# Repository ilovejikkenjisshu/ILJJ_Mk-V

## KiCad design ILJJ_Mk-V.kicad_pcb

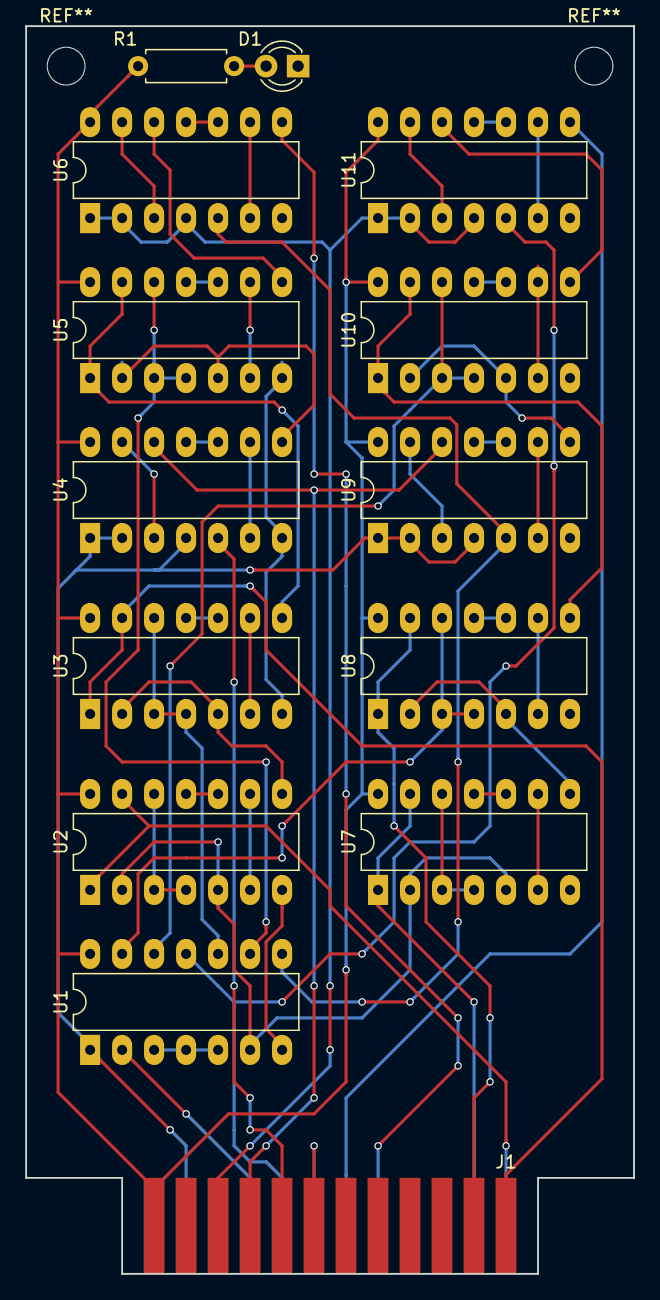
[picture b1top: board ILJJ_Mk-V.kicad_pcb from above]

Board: 2 copper layers, 48.3 x 99.1 mm, 14 parts (0 on the bottom side), 55 nets.

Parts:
D1: POWER; LED_D3.0mm
J1: Conn_02x12; 5530843-1_edge
R1: R; R_Axial_DIN0207_L6.3mm_D2.5mm_P7.62mm_Horizontal
U1, U2, U3, U4, U5, U6, U7, U8, U9, U10, U11: 74LS00; DIP-14_W7.62mm_LongPads

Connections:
/A0: J1.23, U3.1, U3.13
/A1: J1.21, U8.1, U8.13
/B0: J1.24, U2.1, U2.13
/B1: J1.22, U7.1, U7.13
/Cin: J1.9, U4.5
/Cout: J1.10, U1.11, U11.5
/F0: J1.7, J1.8, U1.2, U4.12, U9.12
/F1: J1.5, J1.6, U6.1, U6.2, U6.4, U11.1, U11.2, U11.4
/F2: J1.3, J1.4, U1.1, U4.1, U4.2, U4.4, U9.1, U9.2, U9.4
/FA0_B: U2.8, U3.2, U3.5
/FA0_Cin: U4.8, U5.2, U5.5
/FA0_S: U5.8, U6.12
/FA1_B: U7.8, U8.2, U8.5
/FA1_Cin: U9.8, U10.2, U10.5
/FA1_S: U10.8, U11.12
/IBC: U1.8, U6.5, U9.5
/S0: J1.16, U6.8
/S1: J1.14, U11.8
/SUB_FLAG: U1.6, U2.2, U2.5, U7.2, U7.5
GND: D1.1, J1.11, J1.12, U1.7, U2.7, U3.7, U4.7, U5.7, U6.7, U7.7, U8.7, U9.7, U10.7, U11.7
unnamed: D1.2, R1.2
unnamed: U1.3, U1.4, U1.5
unnamed: U1.9, U5.3, U5.4, U5.12
unnamed: U1.10, U3.3, U3.4, U3.12
unnamed: U1.12, U10.3, U10.4, U10.12
unnamed: U1.13, U8.3, U8.4, U8.12
unnamed: U2.6, U2.9
unnamed: U2.10, U2.11
unnamed: U2.3, U2.4, U2.12
unnamed: U3.6, U3.9
unnamed: U3.8, U5.1, U5.13
unnamed: U3.10, U3.11
unnamed: U4.6, U4.9
unnamed: U4.10, U4.11
unnamed: U4.3, U4.13
unnamed: U5.6, U5.9
unnamed: U5.10, U5.11
unnamed: U6.6, U6.9
unnamed: U6.10, U6.11
unnamed: U6.3, U6.13
unnamed: U7.6, U7.9
unnamed: U7.10, U7.11
unnamed: U7.3, U7.4, U7.12
unnamed: U8.6, U8.9
unnamed: U8.10, U8.11
unnamed: U9.6, U9.9
unnamed: U9.10, U9.11
unnamed: U9.3, U9.13
unnamed: U8.8, U10.1, U10.13
unnamed: U10.6, U10.9
unnamed: U10.10, U10.11
unnamed: U11.6, U11.9
unnamed: U11.10, U11.11
unnamed: U11.3, U11.13
VCC: J1.1, J1.2, R1.1, U1.14, U2.14, U3.14, U4.14, U5.14, U6.14, U7.14, U8.14, U9.14, U10.14, U11.14

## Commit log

2018-10-15 [add] 基本的な回路図
    アノテーションはまだ
2018-10-15 [add] アノテーションとIC電源
    ERCも通した
2018-10-15 [add] カードエッジ部のフットプリント
2018-10-16 [add] 基板設計図
2018-10-30 [add] #2 ネジ穴を追加
    パーツこれであってるのかわからんけどw
2018-10-30 [fix] カードエッジ部のフットプリントを修正
    なぜかSMDパッドにしてたけどちゃんとコネクタパッドにできるんすね
2018-10-30 [add] #1 パワーランプ
    抵抗のフットプリントこれでいいのかちょっとあやしい
